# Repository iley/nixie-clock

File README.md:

Yet another nixie clock
=======================

This repo contains hardware design files and firmware source code for a nixie tube clock.

The clock uses soviet IN-12 tubes and K155ID1 driver ICs.

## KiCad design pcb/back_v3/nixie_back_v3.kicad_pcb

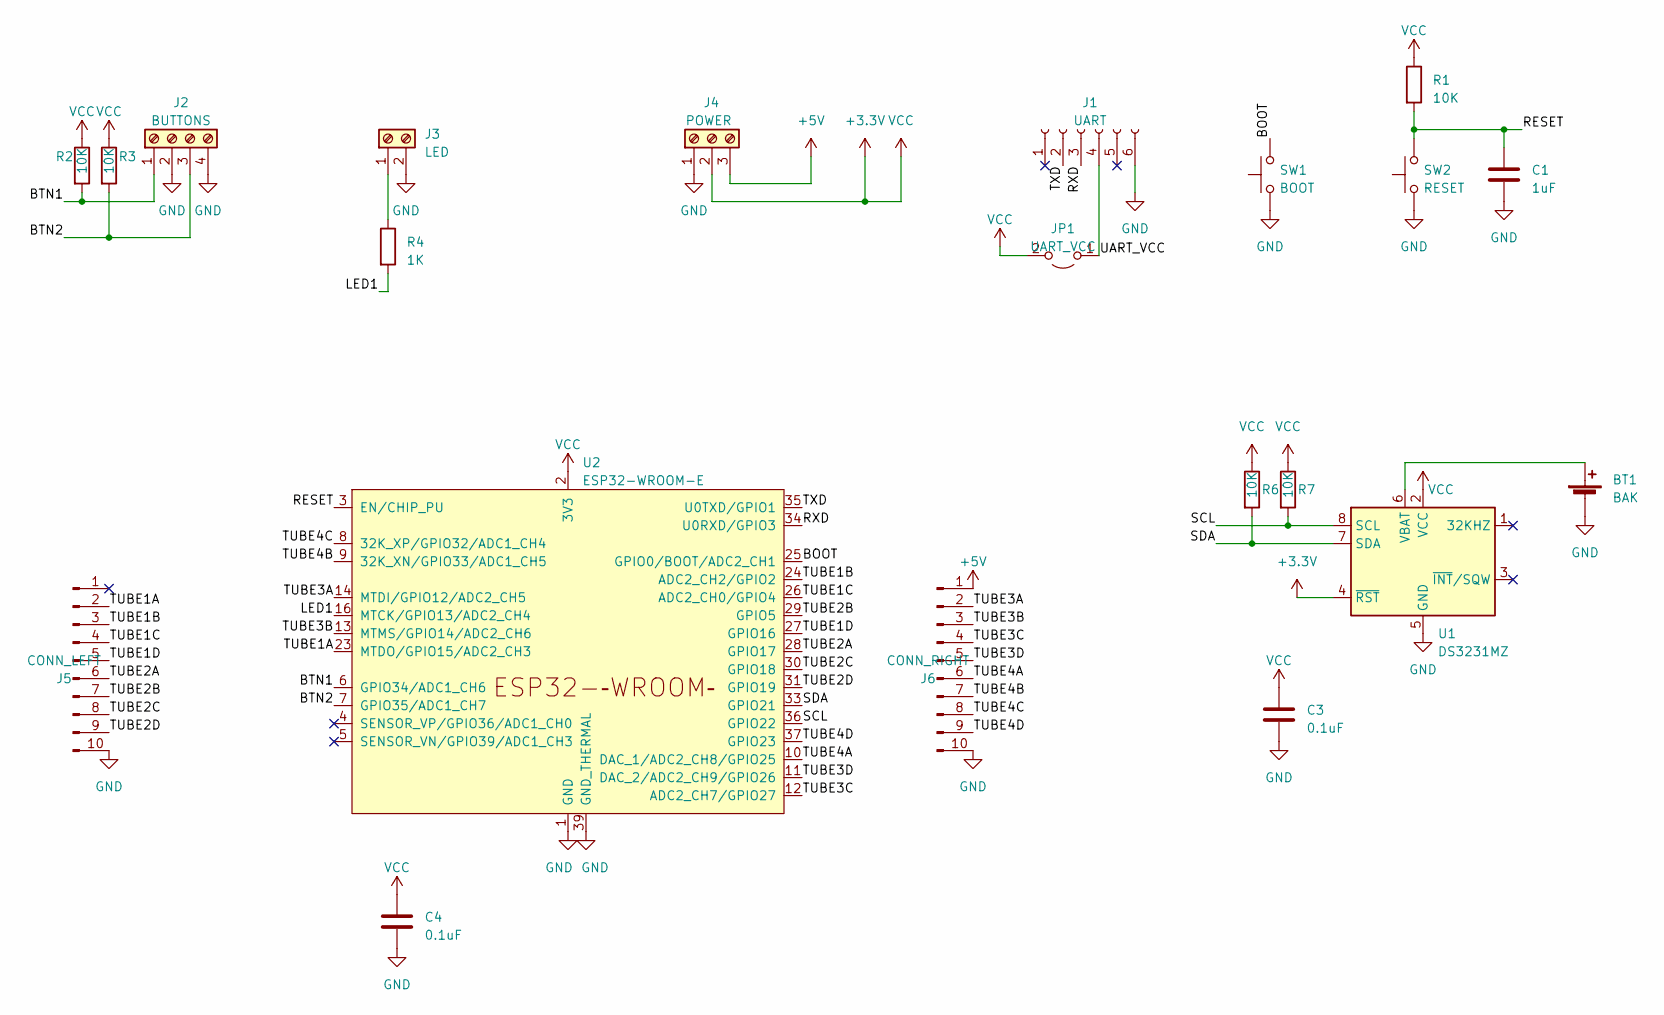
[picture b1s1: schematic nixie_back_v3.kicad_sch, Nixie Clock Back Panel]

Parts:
BT1: BAK; BatteryHolder_Keystone_103_1x20mm
C1: 1uF; C_1206_3216Metric_Pad1.33x1.80mm_HandSolder
C3, C4: 0.1uF; C_1206_3216Metric_Pad1.33x1.80mm_HandSolder
J1: UART; PinHeader_1x06_P2.54mm_Vertical
J2: BUTTONS; TerminalBlock_Altech_AK300-4_P5.00mm
J3: LED; TerminalBlock_Altech_AK300-2_P5.00mm
J4: POWER; TerminalBlock_Altech_AK300-3_P5.00mm
J5: CONN_LEFT; PinSocket_1x10_P2.54mm_Vertical
J6: CONN_RIGHT; PinSocket_1x10_P2.54mm_Vertical
JP1: UART_VCC; PinHeader_1x02_P2.54mm_Vertical
R1, R2, R3, R6, R7: 10K; R_1206_3216Metric_Pad1.30x1.75mm_HandSolder
R4: 1K; R_1206_3216Metric_Pad1.30x1.75mm_HandSolder
SW1: BOOT; SW_Push_1P1T_XKB_TS-1187A
SW2: RESET; SW_Push_1P1T_XKB_TS-1187A
U1: DS3231MZ; SOIC-8_3.9x4.9mm_P1.27mm
U2: ESP32-WROOM-E; ESP32-WROOM-32E

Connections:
+3.3V: C3.1, C4.1, J4.2, JP1.2 (B), R1.1, R2.1, R3.1, R6.1, R7.1, U1.2 (VCC), U1.4 (~RST), U2.2 (3V3)
+5V: J4.3, J6.1
/BOOT: SW1.2, U2.25 (GPIO0/BOOT/ADC2_CH1)
/BTN1: J2.1, R2.2, U2.6 (GPIO34/ADC1_CH6)
/BTN2: J2.3, R3.2, U2.7 (GPIO35/ADC1_CH7)
/LED1: R4.2, U2.16 (MTCK/GPIO13/ADC2_CH4)
/RESET: C1.1, R1.2, SW2.2, U2.3 (EN/CHIP_PU)
/RXD: J1.3, U2.34 (U0RXD/GPIO3)
/SCL: R7.2, U1.8 (SCL), U2.36 (GPIO22)
/SDA: R6.2, U1.7 (SDA), U2.33 (GPIO21)
/TUBE1A: J5.2, U2.23 (MTDO/GPIO15/ADC2_CH3)
/TUBE1B: J5.3, U2.24 (ADC2_CH2/GPIO2)
/TUBE1C: J5.4, U2.26 (ADC2_CH0/GPIO4)
/TUBE1D: J5.5, U2.27 (GPIO16)
/TUBE2A: J5.6, U2.28 (GPIO17)
/TUBE2B: J5.7, U2.29 (GPIO5)
/TUBE2C: J5.8, U2.30 (GPIO18)
/TUBE2D: J5.9, U2.31 (GPIO19)
/TUBE3A: J6.2, U2.14 (MTDI/GPIO12/ADC2_CH5)
/TUBE3B: J6.3, U2.13 (MTMS/GPIO14/ADC2_CH6)
/TUBE3C: J6.4, U2.12 (ADC2_CH7/GPIO27)
/TUBE3D: J6.5, U2.11 (DAC_2/ADC2_CH9/GPIO26)
/TUBE4A: J6.6, U2.10 (DAC_1/ADC2_CH8/GPIO25)
/TUBE4B: J6.7, U2.9 (32K_XN/GPIO33/ADC1_CH5)
/TUBE4C: J6.8, U2.8 (32K_XP/GPIO32/ADC1_CH4)
/TUBE4D: J6.9, U2.37 (GPIO23)
/TXD: J1.2, U2.35 (U0TXD/GPIO1)
/UART_VCC: J1.4, JP1.1 (A)
GND: BT1.2 (-), C1.2, C3.2, C4.2, J1.6, J2.2, J2.4, J3.2, J4.1, J5.10, J6.10, SW1.1, SW2.1, U1.5 (GND), U2.1 (GND), U2.15 (GND), U2.38 (GND), U2.39 (GND_THERMAL)
unnamed: BT1.1 (+), U1.6 (VBAT)
unnamed: J3.1, R4.1

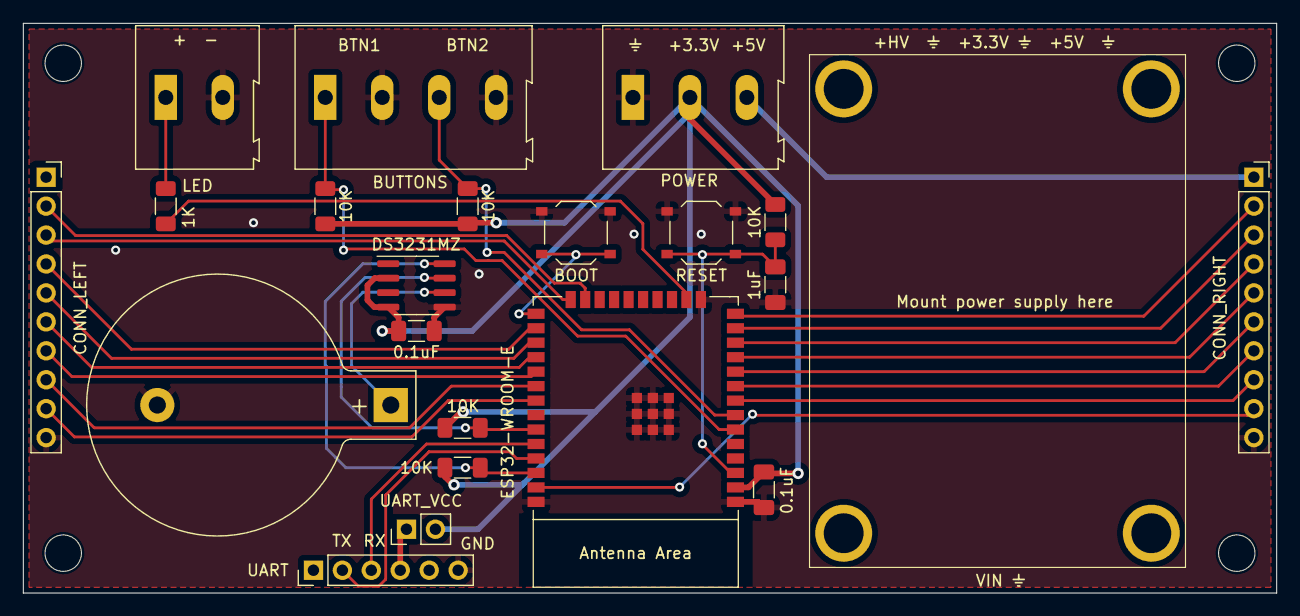
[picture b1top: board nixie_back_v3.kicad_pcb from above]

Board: 2 copper layers, 110.0 x 50.0 mm, 21 parts (0 on the bottom side), 31 nets.

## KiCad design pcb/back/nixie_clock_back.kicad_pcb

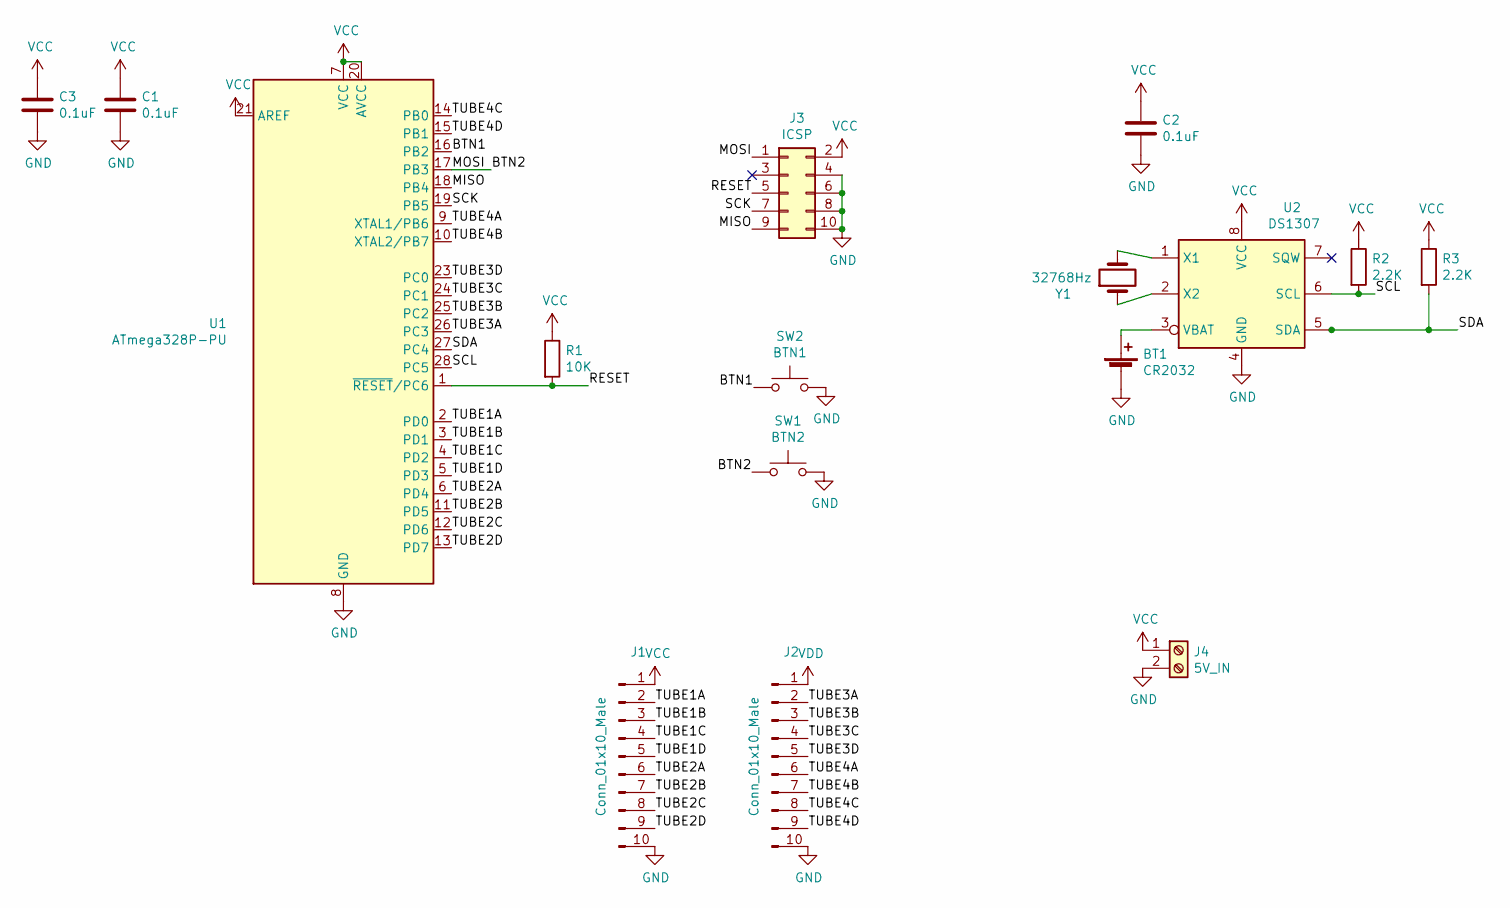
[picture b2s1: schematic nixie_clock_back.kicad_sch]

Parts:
BT1: CR2032; BatteryHolder_Keystone_103_1x20mm
C1, C2, C3: 0.1uF; C_Disc_D3.8mm_W2.6mm_P2.50mm
J1, J2: Conn_01x10_Male; PinSocket_1x10_P2.54mm_Vertical
J3: ICSP; Atmel_ISP_Socket_10pin
J4: 5V_IN; Terminal_Block_KF301-5.0-2P
R1: 10K; R_Axial_DIN0207_L6.3mm_D2.5mm_P10.16mm_Horizontal
R2, R3: 2.2K; R_Axial_DIN0207_L6.3mm_D2.5mm_P10.16mm_Horizontal
SW1: BTN2; JST_XH_B2B-XH-A_1x02_P2.50mm_Vertical
SW2: BTN1; JST_XH_B2B-XH-A_1x02_P2.50mm_Vertical
U1: ATmega328P-PU; DIP-28_W7.62mm
U2: DS1307; DIP-8_W7.62mm
Y1: 32768Hz; Crystal_C38-LF_D3.0mm_L8.0mm_Horizontal

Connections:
/BTN1: SW2.1, U1.16 (PB2)
/BTN2: J3.1, SW1.1, U1.17 (PB3)
/MISO: J3.9, U1.18 (PB4)
/RESET: J3.5, R1.2, U1.1 (~RESET/PC6)
/SCK: J3.7, U1.19 (PB5)
/SCL: R2.2, U1.28 (PC5), U2.6 (SCL)
/SDA: R3.2, U1.27 (PC4), U2.5 (SDA)
/TUBE1A: J1.2, U1.2 (PD0)
/TUBE1B: J1.3, U1.3 (PD1)
/TUBE1C: J1.4, U1.4 (PD2)
/TUBE1D: J1.5, U1.5 (PD3)
/TUBE2A: J1.6, U1.6 (PD4)
/TUBE2B: J1.7, U1.11 (PD5)
/TUBE2C: J1.8, U1.12 (PD6)
/TUBE2D: J1.9, U1.13 (PD7)
/TUBE3A: J2.2, U1.26 (PC3)
/TUBE3B: J2.3, U1.25 (PC2)
/TUBE3C: J2.4, U1.24 (PC1)
/TUBE3D: J2.5, U1.23 (PC0)
/TUBE4A: J2.6, U1.9 (XTAL1/PB6)
/TUBE4B: J2.7, U1.10 (XTAL2/PB7)
/TUBE4C: J2.8, U1.14 (PB0)
/TUBE4D: J2.9, U1.15 (PB1)
GND: BT1.2 (-), C1.2, C2.2, C3.2, J1.10, J2.10, J3.4, J3.6, J3.8, J3.10, J4.2, SW1.2, SW2.2, U1.8 (GND), U1.22 (GND), U2.4 (GND)
unnamed: BT1.1 (+), U2.3 (VBAT)
unnamed: U2.1 (X1), Y1.2
unnamed: U2.2 (X2), Y1.1
VCC: C1.1, C2.1, C3.1, J1.1, J3.2, J4.1, R1.1, R2.1, R3.1, U1.7 (VCC), U1.20 (AVCC), U1.21 (AREF), U2.8 (VCC)
VDD: J2.1

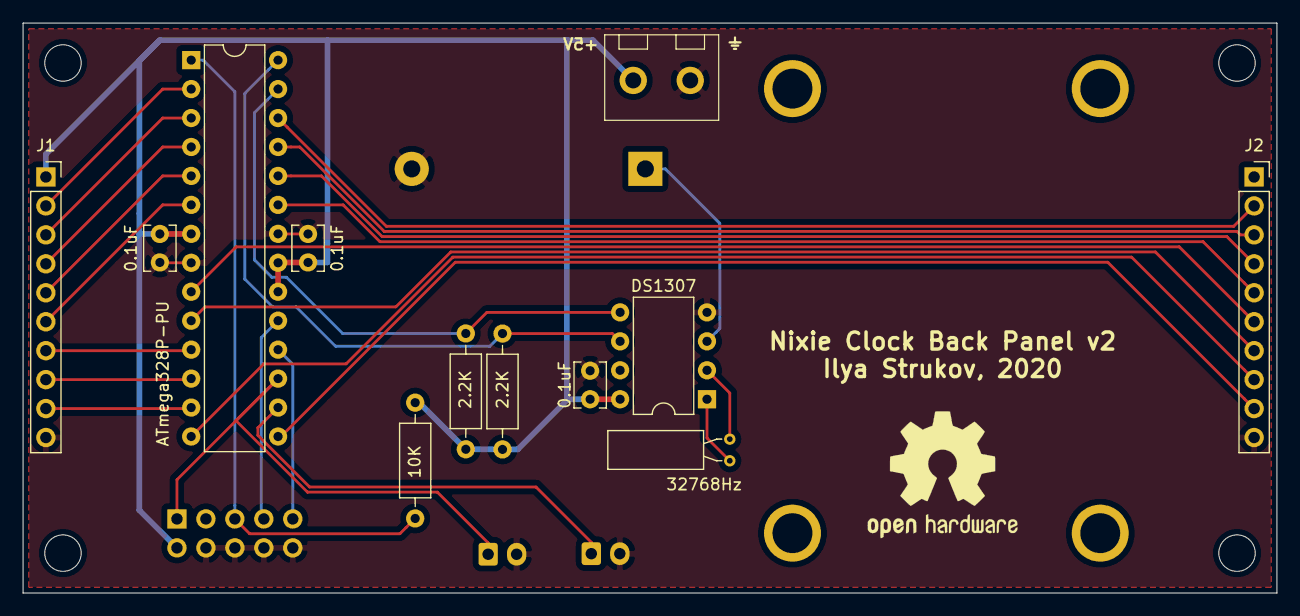
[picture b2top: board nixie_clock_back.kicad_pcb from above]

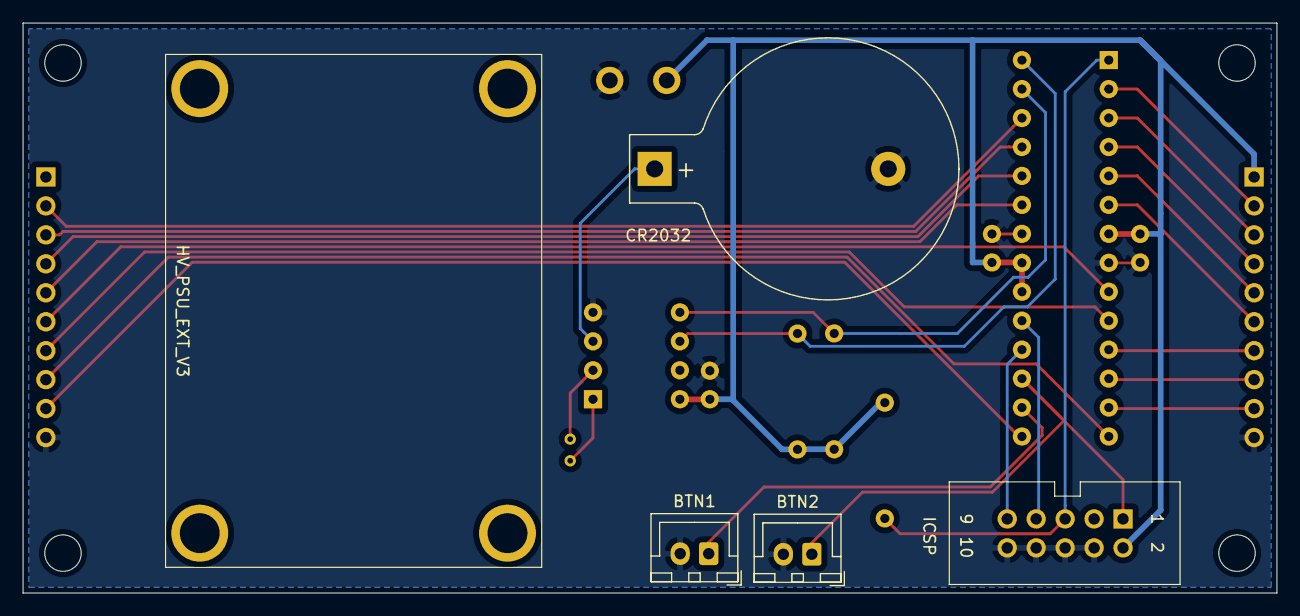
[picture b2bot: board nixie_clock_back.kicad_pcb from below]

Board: 2 copper layers, 110.0 x 50.0 mm, 16 parts (4 on the bottom side), 28 nets.

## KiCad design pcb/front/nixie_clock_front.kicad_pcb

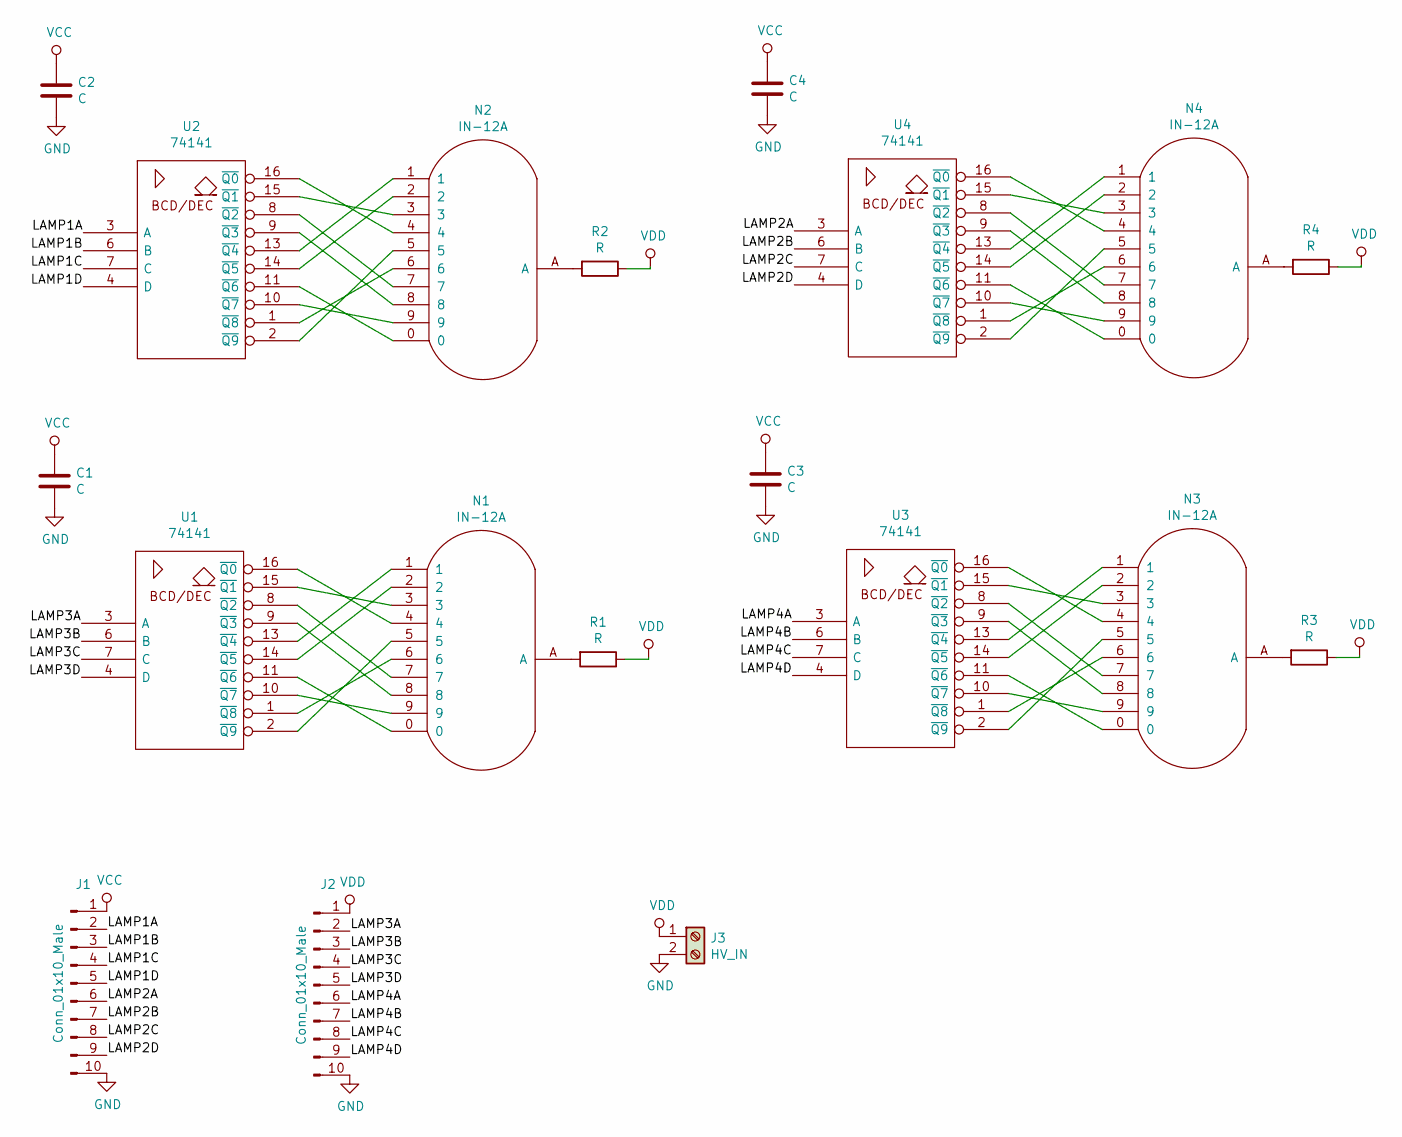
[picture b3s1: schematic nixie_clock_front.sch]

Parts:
C1, C2, C3, C4: C; C_Disc_D3.8mm_W2.6mm_P2.50mm
J1, J2: Conn_01x10_Male; PinHeader_1x10_P2.54mm_Vertical
J3: HV_IN; Terminal_Block_KF301-5.0-2P
N1, N2, N3, N4: IN-12A
R1, R2, R3, R4: R; R_Axial_DIN0207_L6.3mm_D2.5mm_P10.16mm_Horizontal
U1, U2, U3, U4: 74141; DIP-16_W7.62mm

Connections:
/LAMP1A: J1.2, U2.3 (A)
/LAMP1B: J1.3, U2.6 (B)
/LAMP1C: J1.4, U2.7 (C)
/LAMP1D: J1.5, U2.4 (D)
/LAMP2A: J1.6, U4.3 (A)
/LAMP2B: J1.7, U4.6 (B)
/LAMP2C: J1.8, U4.7 (C)
/LAMP2D: J1.9, U4.4 (D)
/LAMP3A: J2.2, U1.3 (A)
/LAMP3B: J2.3, U1.6 (B)
/LAMP3C: J2.4, U1.7 (C)
/LAMP3D: J2.5, U1.4 (D)
/LAMP4A: J2.6, U3.3 (A)
/LAMP4B: J2.7, U3.6 (B)
/LAMP4C: J2.8, U3.7 (C)
/LAMP4D: J2.9, U3.4 (D)
GND: C1.2, C2.2, C3.2, C4.2, J1.10, J2.10, J3.2, U1.12 (GND), U2.12 (GND), U3.12 (GND), U4.12 (GND)
unnamed: N1.0, U1.11 (~Q6)
unnamed: N1.1, U1.13 (~Q4)
unnamed: N1.2, U1.14 (~Q5)
unnamed: N1.3, U1.15 (~Q1)
unnamed: N1.4, U1.16 (~Q0)
unnamed: N1.5, U1.2 (~Q9)
unnamed: N1.6, U1.1 (~Q8)
unnamed: N1.7, U1.8 (~Q2)
unnamed: N1.8, U1.9 (~Q3)
unnamed: N1.9, U1.10 (~Q7)
unnamed: N1.A, R1.2
unnamed: N2.0, U2.11 (~Q6)
unnamed: N2.1, U2.13 (~Q4)
unnamed: N2.2, U2.14 (~Q5)
unnamed: N2.3, U2.15 (~Q1)
unnamed: N2.4, U2.16 (~Q0)
unnamed: N2.5, U2.2 (~Q9)
unnamed: N2.6, U2.1 (~Q8)
unnamed: N2.7, U2.8 (~Q2)
unnamed: N2.8, U2.9 (~Q3)
unnamed: N2.9, U2.10 (~Q7)
unnamed: N2.A, R2.2
unnamed: N3.0, U3.11 (~Q6)
unnamed: N3.1, U3.13 (~Q4)
unnamed: N3.2, U3.14 (~Q5)
unnamed: N3.3, U3.15 (~Q1)
unnamed: N3.4, U3.16 (~Q0)
unnamed: N3.5, U3.2 (~Q9)
unnamed: N3.6, U3.1 (~Q8)
unnamed: N3.7, U3.8 (~Q2)
unnamed: N3.8, U3.9 (~Q3)
unnamed: N3.9, U3.10 (~Q7)
unnamed: N3.A, R3.2
unnamed: N4.0, U4.11 (~Q6)
unnamed: N4.1, U4.13 (~Q4)
unnamed: N4.2, U4.14 (~Q5)
unnamed: N4.3, U4.15 (~Q1)
unnamed: N4.4, U4.16 (~Q0)
unnamed: N4.5, U4.2 (~Q9)
unnamed: N4.6, U4.1 (~Q8)
unnamed: N4.7, U4.8 (~Q2)
unnamed: N4.8, U4.9 (~Q3)
unnamed: N4.9, U4.10 (~Q7)
unnamed: N4.A, R4.2
VCC: C1.1, C2.1, C3.1, C4.1, J1.1, U1.5 (VCC), U2.5 (VCC), U3.5 (VCC), U4.5 (VCC)
VDD: J2.1, J3.1, R1.1, R2.1, R3.1, R4.1

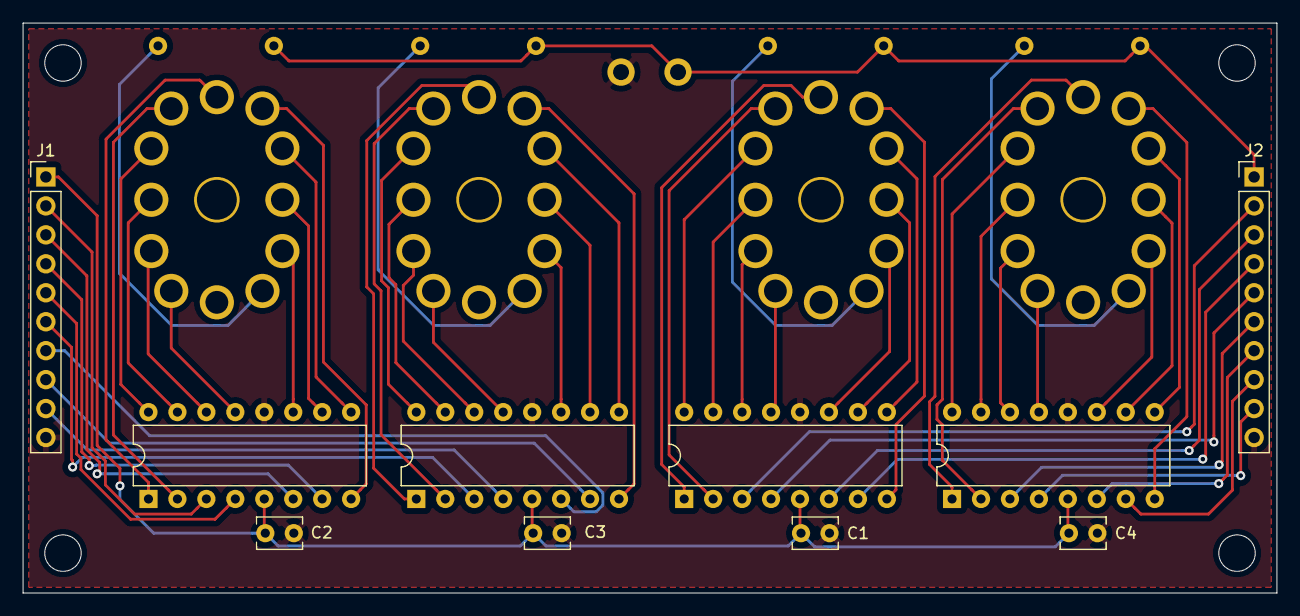
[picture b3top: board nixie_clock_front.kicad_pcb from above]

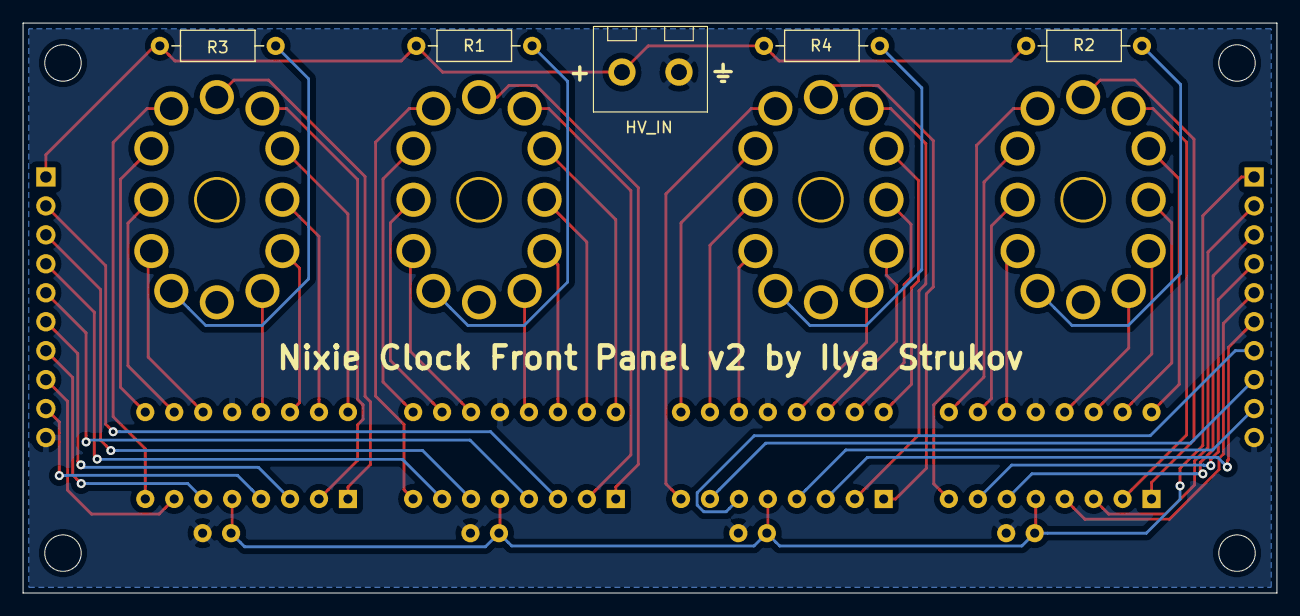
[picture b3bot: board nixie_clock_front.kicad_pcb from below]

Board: 2 copper layers, 110.0 x 50.0 mm, 19 parts (5 on the bottom side), 63 nets.

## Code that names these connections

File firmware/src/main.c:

#include <stdbool.h>
#include <stdint.h>

#include <avr/interrupt.h>
#include <avr/io.h>
#include <util/delay.h>

#include "rtc.h"

#define MAX(x, y) ((x) > (y) ? (x) : (y))
#define MIN(x, y) ((x) < (y) ? (x) : (y))

// How many digits the clock has.
#define DIGITS_COUNT 4

// Blinking delay when setting time.
#define BLINK_MS 250

// Start timer at 65536-1000 for 1ms delay at 8MHz with prescaler 8.
#define TIMER_START 64536

// PB0, PB1, PB6, PB7 -> TUBE4
#define OUT_MASK_B ((1<<PB0) | (1<<PB1) | (1<<PB6) | (1<<PB7))

// PC0-PC3 -> TUBE3
#define OUT_MASK_C 0x0f

// PD0-PD3 -> TUBE1, PD4-PD7 -> TUBE2
#define OUT_MASK_D 0xff

// Maps from digit value to Nixie pin number.
const uint8_t digit_map[] = { 6, 4, 5, 1, 0, 9, 8, 2, 3, 7, 0xf };

// Milliseconds since boot.
uint32_t millis = 0;

// Set up timer 1 to trigger an interrupt every millisecond.
void init_timer() {
    TCCR1A = 0x00;
    TIMSK1 = (1 << TOIE1) ; // Timer 1 overflow interrupt.
    TCNT1 = TIMER_START;
    TCCR1B = (1<<CS11);    // Prescaler 8 => 1MHz
    sei();
}

ISR(TIMER1_OVF_vect) {
    millis++;
    TCNT1 = TIMER_START;
}

// Configure GPIO for tubes and buttons.
void init_pins() {
    DDRB = OUT_MASK_B;
    DDRC = OUT_MASK_C;
    DDRD = OUT_MASK_D;
    PORTB |= (1<<PB2) | (1<<PB3);  // Enable pull-ups for buttons.
}

// Write to the BCD decoders.
void write_tubes(uint8_t tube1, uint8_t tube2, uint8_t tube3, uint8_t tube4) {
    PORTB = (PORTB & ~OUT_MASK_B) | (tube4 & 0x3) << 6 | (tube4 & 0xc) >> 2;
    PORTC = (PORTC & ~OUT_MASK_C) |
        (tube3 & 8) >> 3 | (tube3 & 4) >> 1 | (tube3 & 2) << 1 | (tube3 & 1) << 3;
    PORTD = (PORTD & ~OUT_MASK_D) | (tube2 << 4) | tube1;
}

// Display digits on the tubes. 10 == off.
void write_digits(uint8_t digit1, uint8_t digit2, uint8_t digit3, uint8_t digit4) {
    write_tubes(digit_map[digit1], digit_map[digit2], digit_map[digit3], digit_map[digit4]);
}

typedef struct {
    // Whether the button was pressed before last update.
    bool was_pressed;
    // Whether the button is pressed now.
    bool pressed;
    // Milliseconds since boot when last state change happened.
    uint32_t last_change_millis;
} button_t;

void button_init(button_t* btn) {
    btn->was_pressed = false;
    btn->pressed = false;
    btn->last_change_millis = 0;
}

void button_update(button_t* btn, bool input) {
    btn->was_pressed = btn->pressed;
    // Debouncing: if last state change happened within 100ms, do nothing.
    if (millis - btn->last_change_millis < 100) {
        return;
    }
    btn->pressed = input;
    if (btn->was_pressed != btn->pressed) {
        btn->last_change_millis = millis;
    }
}

// Read digits from datatime into an array.
void get_datetime_digits(datetime_t *dt, uint8_t *digits) {
    digits[0] = dt->hours >> 4;
    digits[1] = dt->hours & 0xf;
    digits[2] = dt->minutes >> 4;
    digits[3] = dt->minutes & 0xf;
}

// Set datatime from an array of digits.
void set_datetime_digits(datetime_t *dt, uint8_t *digits) {
    dt->hours = (digits[0] << 4) | digits[1];
    dt->minutes = (digits[2] << 4) | digits[3];
    dt->seconds = 0;
}

int main() {
    init_timer();
    init_pins();
    rtc_init();

    bool running = true;

    datetime_t dt;
    rtc_get(&dt); // Read initial time.

    button_t left_button;
    button_init(&left_button);
    button_t right_button;
    button_init(&right_button);

    // Digits to display: HHMM.
    static uint8_t digits[DIGITS_COUNT];

    // State for setting the time.
    uint8_t current_digit;            // What digit we're setting right now.
    uint32_t setting_start_millis;    // When we started setting time, for blinking.

    while (true) {
        // Read the button status.
        button_update(&left_button, (PINB & (1<<PB3)) == 0);
        button_update(&right_button, (PINB & (1<<PB2)) == 0);

        // Whether the buttons were pushed up.
        bool left_button_up = (!left_button.pressed && left_button.was_pressed);
        bool right_button_up = (!right_button.pressed && right_button.was_pressed);

        if (running) {
            rtc_get(&dt);
            get_datetime_digits(&dt, digits);

            if (left_button_up || right_button_up) {
                // If any button is pressed, enter timesetting mode.
                running = false;
                // Start setting time from left-most digit.
                current_digit = 0;
                // Track when this mode was entered, for blinking.
                setting_start_millis = millis;
            }
        } else {
            get_datetime_digits(&dt, digits);

            // Left button switches between digits.
            if (left_button_up) {
                if (current_digit < DIGITS_COUNT-1) {
                    // Advance to next digit.
                    current_digit++;
                } else {
                    // We scrolled through all digits. Finish setting the time.
                    rtc_set(&dt);
                    running = true;
                }
            } else if (right_button_up) {
                // Determine the upper limit for current digit.
                uint8_t limit = 10;
                if (current_digit == 0) {
                    // First digit can be either 0, 1 or 2.
                    limit = 3;
                } else if (current_digit == 1 && digits[0] == 2) {
                    // If first digit is 2, second one can only go up to 3.
                    limit = 4;
                } else if (current_digit == 2) {
                    limit = 6;
                }
                // Cycle through possible digit values.
                digits[current_digit] = (digits[current_digit] + 1) % limit;

                // When the first digit changes, second digit might go out of range.
                if (digits[0] == 2) {
                    digits[1] = MIN(digits[1], 3);
                }
            }

            // Save the current digits in datetime.
            set_datetime_digits(&dt, digits);

            // Blink the current digit.
            if (((millis - setting_start_millis) / BLINK_MS) % 2 == 1) {
                digits[current_digit] = 10;
            }
        }

        write_digits(digits[0], digits[1], digits[2], digits[3]);
    }
}

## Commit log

2019-10-19 start
2019-10-19 Front PCB schematic
2019-10-19 Front panel PCB layout
2019-10-19 Generate gerbers
2019-10-19 Start the back PCB
2019-10-20 Add license file
2019-10-20 Back panel PCB
2019-11-09 Final PCB tweaks
2019-11-09 Skeleton of the firmware
2019-11-09 DS-1307 communication
2019-11-10 Add case Fusion 360 model
2019-11-10 Random PCB changes
2019-11-12 Improve the case
2019-11-16 Track time since boot using timer interrupts
2019-11-16 Handle buttons
2019-11-16 Add missing PCB trace
2019-11-16 Time setting routine
2019-11-16 Comments
2019-11-17 More comments
2019-12-16 Fix a bug in time setting routine
2020-01-18 Fix minor issues on the back PCB
2020-01-18 Add shell v2
2020-02-15 Add readme and license
2020-02-15 Code formatting and a missing #include
2020-02-15 Clean up
2021-04-24 Replace PlatformIO with make+docker
2022-11-15 Update the Docker image
2022-11-15 Add screensaver routine every hour
2022-11-16 Update back PCB schematic
2022-11-17 Tweak screensaver delay
2022-11-26 Move v1 firmware to a subdir
2022-11-26 Pico SDK setup
2022-11-26 Pico PIO test
2022-11-27 Basic DS1302 operation
2022-11-27 Enable trickle charging
2022-11-28 Code cleanup
2023-02-11 back pcb: upgrade to kicad 6, add measurements
2023-02-11 Random changes in the v2 firmware prototype
2023-02-11 Start v2 back pcb
2023-04-23 Schematic for back PCB v2
2023-04-30 Lay out the new back panel pcb
2023-04-30 Rename kicad project
2023-04-30 Add gerbers directory
2023-05-28 Update front PCB to newer KiCAD version
2023-05-28 Fix pin assignment on v3 back pcb
    GPIO pins 34-39 on ESP32 are input only.
2023-05-28 Dummy ESP32 firmware
2023-06-10 Misc PCB changes
2023-06-10 Update pin numbers
2023-06-15 Add design files for v3
2023-06-19 Synchronize time every midnight
2023-06-19 Implement NTP sync
2023-06-19 Make some progress on the firmware
2026-03-08 I dunno
2026-03-08 Fix DST switch
2026-03-08 Fix example_secret_wifi.h
2026-03-09 OTA updates
2026-03-09 Update readme for the esp32 firmware
2026-03-09 Time setting logic
2026-03-09 Add manual sync button
2026-03-09 Disable manual NTP sync when WiFi not available
2026-03-09 Animation on manual NTP sync
